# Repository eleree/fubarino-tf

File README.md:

# fubarino-tf
a fork of fubarino v1.5 using a easy solider tf socket and a more common USB socket

use the CAM processor scripts in directory jlc to export gerbers for JLC.

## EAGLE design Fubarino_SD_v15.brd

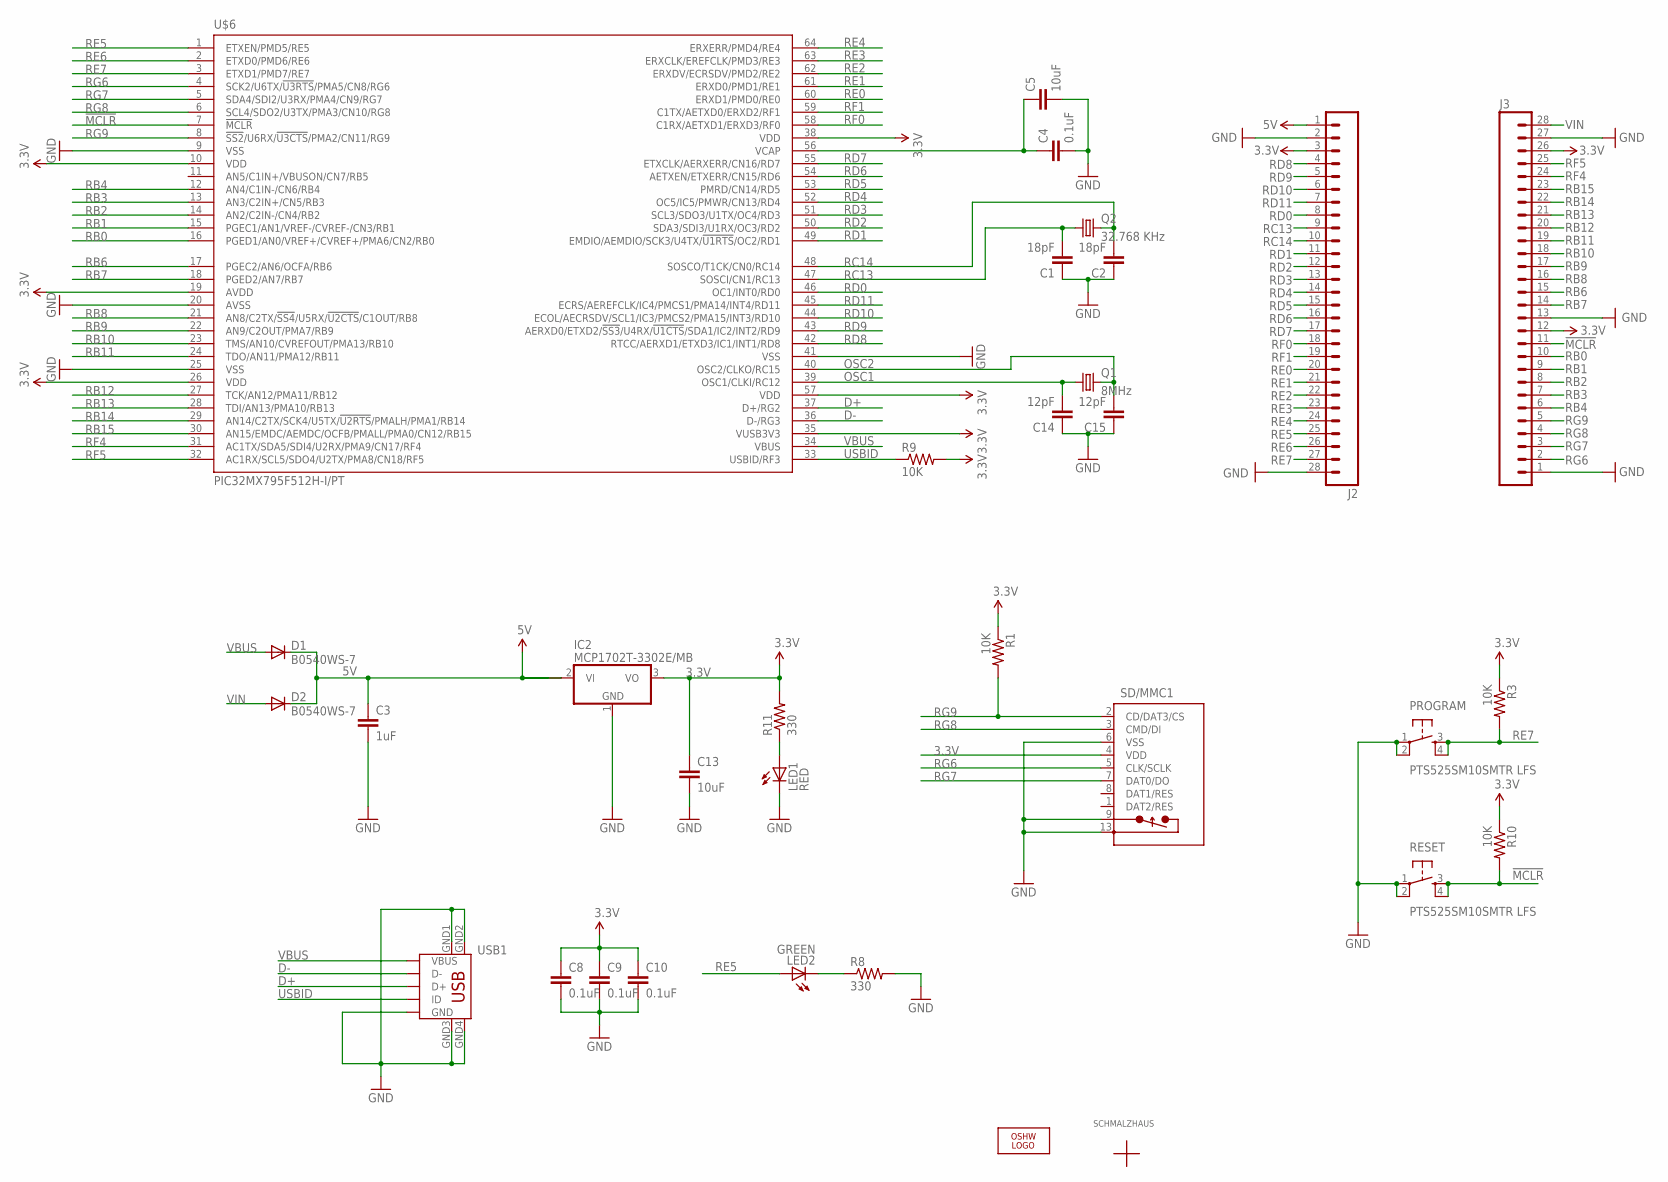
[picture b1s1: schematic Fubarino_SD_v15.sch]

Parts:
C1, C2: 18pF; 0603-CAP
C3: 1uF; 0603-CAP
C4, C8, C9: 0.1uF; 0603-CAP
C5, C13: 10uF; 0805
C10: 0.1uF; 0603
C14, C15: 12pF; 0603-CAP
D1, D2: B0540WS-7; SOD-323
IC2: MCP1702T-3302E/MB; SOT89
J2: M28USEPIN1; 1X28
J3: M28NOPIN1; 1X28_NO_PIN_1
LED1: RED; LED-0603
LED2: GREEN; LED-0603
LOGO1: OSHW_LOGO_8MILX0070-NT; OSHW_8X70_NOTEXT
PROGRAM: PTS525SM10SMTR LFS; TACTILE_SWITCH_SMD
Q1: 8MHz; NX5032_5MM_3.2MM_CRYSTAL
Q2: 32.768 KHz; TC26H
R1, R3, R9, R10: 10K; 0603-RES
R8, R11: 330; 0603-RES
RESET: PTS525SM10SMTR LFS; TACTILE_SWITCH_SMD
SD/MMC1: MICRO_SD/MMC_CP_NEWTFC-WPAPR-08; TFC-WPAPR-08
U$1: SCHMALZHAUSSCHMALZHAUS_SMALL; SCHMALZHAUS_SMALL
U$2: CE_MARK5MM; CE_5MM
U$3: ROHS_GARBAGE; ROHS_GARBAGE_5MM
U$4, U$5: CHIPKIT2MM; CHIPKIT_2MM
U$6: PIC32MX795F512H-I/PT; TQFP64-10X10
USB1: MINI_USB9SMALLER_CREAM; USB_MINI_9PIN-SMALLER_CREAM

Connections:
3.3V: C8.1, C9.1, C10.1, C13.1, IC2.3 (VO), J2.3, J3.12, J3.26, R1.1, R3.1, R9.2, R10.1, R11.2, SD/MMC1.4 (VDD), U$6.10 (VDD), U$6.19 (AVDD), U$6.26 (VDD), U$6.35 (VUSB3V3), U$6.38 (VDD), U$6.57 (VDD)
5V: C3.1, D1.1 (C), D2.1 (C), IC2.2 (VI), IC2.2@1 (VI1), J2.1
!MCLR!: J3.11, R10.2, RESET.3, RESET.4, U$6.7 (!MCLR)
D+: U$6.37 (D+/RG2), USB1.D+
D-: U$6.36 (D-/RG3), USB1.D-
GND: C1.1, C2.1, C3.2, C4.2, C5.2, C8.2, C9.2, C10.2, C13.2, C14.1, C15.1, IC2.1 (GND), J2.2, J2.28, J3.1, J3.13, J3.27, LED1.C, PROGRAM.1, PROGRAM.2, R8.2, RESET.1, RESET.2, SD/MMC1.6 (VSS), SD/MMC1.9 (CP_E), SD/MMC1.13 (PACK1), U$6.9 (VSS), U$6.20 (AVSS), U$6.25 (VSS), U$6.41 (VSS), USB1.GND, USB1.GND1, USB1.GND2, USB1.GND3, USB1.GND4
unnamed: LED1.A, R11.1
unnamed: LED2.C, R8.1
unnamed: C4.1, C5.1, U$6.56 (VCAP)
OSC1: C14.2, Q1.1, U$6.39 (OSC1/CLKI/RC12)
OSC2: C15.2, Q1.2, U$6.40 (OSC2/CLKO/RC15)
RB0: J3.10, U$6.16 (PGED1/AN0/VREF+/CVREF+/PMA6/CN2/RB0)
RB1: J3.9, U$6.15 (PGEC1/AN1/VREF-/CVREF-/CN3/RB1)
RB2: J3.8, U$6.14 (AN2/C2IN-/CN4/RB2)
RB3: J3.7, U$6.13 (AN3/C2IN+/CN5/RB3)
RB4: J3.6, U$6.12 (AN4/C1IN-/CN6/RB4)
RB6: J3.15, U$6.17 (PGEC2/AN6/OCFA/RB6)
RB7: J3.14, U$6.18 (PGED2/AN7/RB7)
RB8: J3.16, U$6.21 (AN8/C2TX/!SS4!/U5RX/!U2CTS!/C1OUT/RB8)
RB9: J3.17, U$6.22 (AN9/C2OUT/PMA7/RB9)
RB10: J3.18, U$6.23 (TMS/AN10/CVREFOUT/PMA13/RB10)
RB11: J3.19, U$6.24 (TDO/AN11/PMA12/RB11)
RB12: J3.20, U$6.27 (TCK/AN12/PMA11/RB12)
RB13: J3.21, U$6.28 (TDI/AN13/PMA10/RB13)
RB14: J3.22, U$6.29 (AN14/C2TX/SCK4/U5TX/!U2RTS!/PMALH/PMA1/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)
RB15: J3.23, U$6.30 (AN15/EMDC/AEMDC/OCFB/PMALL/PMA0/CN12/RB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)
RC13: C1.2, J2.9, Q2.1, U$6.47 (SOSCI/CN1/RC13)
RC14: C2.2, J2.10, Q2.2, U$6.48 (SOSCO/T1CK/CN0/RC14)
RD0: J2.8, U$6.46 (OC1/INT0/RD0)
RD1: J2.11, U$6.49 (EMDIO/AEMDIO/SCK3/U4TX/!U1RTS!/OC2/RD1)
RD2: J2.12, U$6.50 (SDA3/SDI3/U1RX/OC3/RD2)
RD3: J2.13, U$6.51 (SCL3/SDO3/U1TX/OC4/RD3)
RD4: J2.14, U$6.52 (OC5/IC5/PMWR/CN13/RD4)
RD5: J2.15, U$6.53 (PMRD/CN14/RD5)
RD6: J2.16, U$6.54 (AETXEN/ETXERR/CN15/RD6)
RD7: J2.17, U$6.55 (ETXCLK/AERXERR/CN16/RD7)
RD8: J2.4, U$6.42 (RTCC/AERXD1/ETXD3/IC1/INT1/RD8)
RD9: J2.5, U$6.43 (AERXD0/ETXD2/!SS3!/U4RX/!U1CTS!/SDA1/IC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)
RD10: J2.6, U$6.44 (ECOL/AECRSDV/SCL1/IC3/PMCS2/PMA15/INT3/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)
RD11: J2.7, U$6.45 (ECRS/AEREFCLK/IC4/PMCS1/PMA14/INT4/RD11)
RE0: J2.20, U$6.60 (ERXD1/PMD0/RE0)
RE1: J2.21, U$6.61 (ERXD0/PMD1/RE1)
RE2: J2.22, U$6.62 (ERXDV/ECRSDV/PMD2/RE2)
RE3: J2.23, U$6.63 (ERXCLK/EREFCLK/PMD3/RE3)
RE4: J2.24, U$6.64 (ERXERR/PMD4/RE4)
RE5: J2.25, LED2.A, U$6.1 (ETXEN/PMD5/RE5)
RE6: J2.26, U$6.2 (ETXD0/PMD6/RE6)
RE7: J2.27, PROGRAM.3, PROGRAM.4, R3.2, U$6.3 (ETXD1/PMD7/RE7)
RF0: J2.18, U$6.58 (C1RX/AETXD1/ERXD3/RF0)
RF1: J2.19, U$6.59 (C1TX/AETXD0/ERXD2/RF1)
RF4: J3.24, U$6.31 (AC1TX/SDA5/SDI4/U2RX/PMA9/CN17/RF4)
RF5: J3.25, U$6.32 (AC1RX/SCL5/SDO4/U2TX/PMA8/CN18/RF5)
RG6: J3.2, SD/MMC1.5 (CLK/SCLK), U$6.4 (SCK2/U6TX/!U3RTS!/PMA5/CN8/RG6)
RG7: J3.3, SD/MMC1.7 (DAT0/DO), U$6.5 (SDA4/SDI2/U3RX/PMA4/CN9/RG7)
RG8: J3.4, SD/MMC1.3 (CMD/DI), U$6.6 (SCL4/SDO2/U3TX/PMA3/CN10/RG8)
RG9: J3.5, R1.2, SD/MMC1.2 (CD/DAT3/CS), U$6.8 (!SS2!/U6RX/!U3CTS!/PMA2/CN11/RG9)
USBID: R9.1, U$6.33 (USBID/RF3), USB1.ID
VBUS: D1.2 (A), U$6.34 (VBUS), USB1.VBUS
VIN: D2.2 (A), J3.28

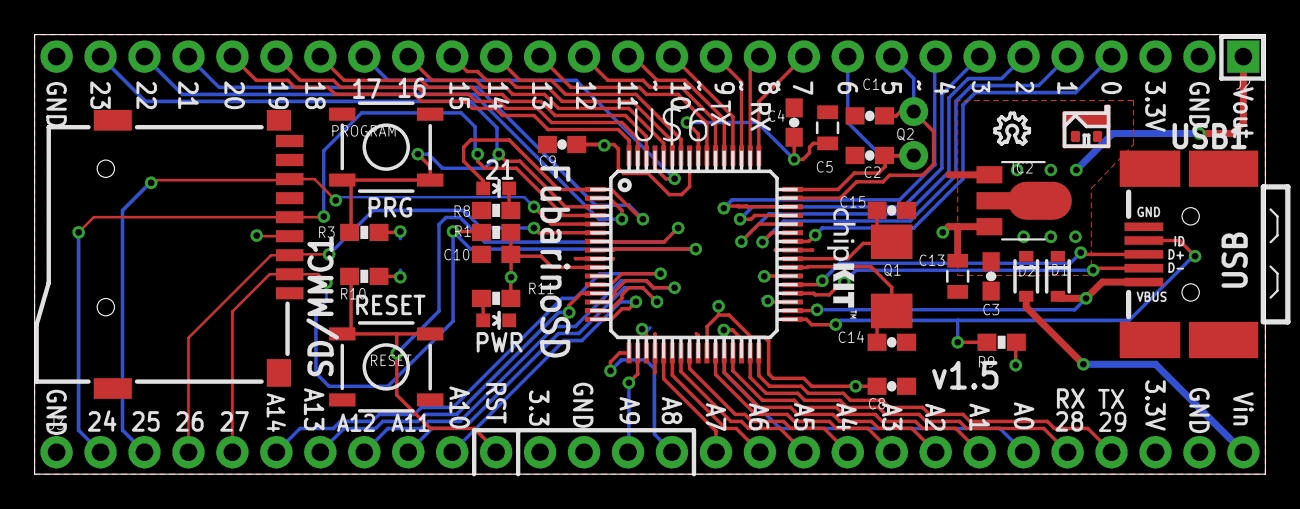
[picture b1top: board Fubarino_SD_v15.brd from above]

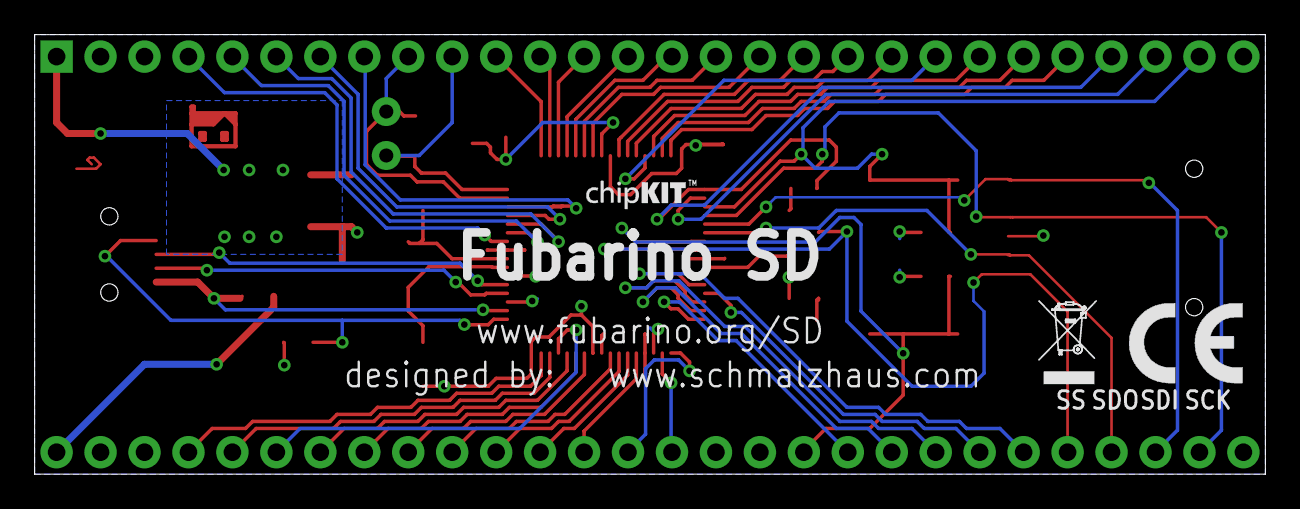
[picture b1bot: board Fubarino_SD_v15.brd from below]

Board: 2 copper layers, 71.1 x 25.4 mm, 38 parts (3 on the bottom side), 59 nets.

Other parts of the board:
DRILEGEND: DRILEGEND

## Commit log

2020-08-27 add pcb & sch

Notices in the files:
Fubarino_SD_v15.brd:
Copyright 2012 Brian Schmalz Copyright and related rights are licensed under the Solderpad Hardware License, Version 0.51 (the “License”);
software, hardware and materials distributed under this License is distributed on an “AS IS” BASIS, WITHOUT WARRANTIES OR CONDITIONS OF ANY KIND, either express or implied.
